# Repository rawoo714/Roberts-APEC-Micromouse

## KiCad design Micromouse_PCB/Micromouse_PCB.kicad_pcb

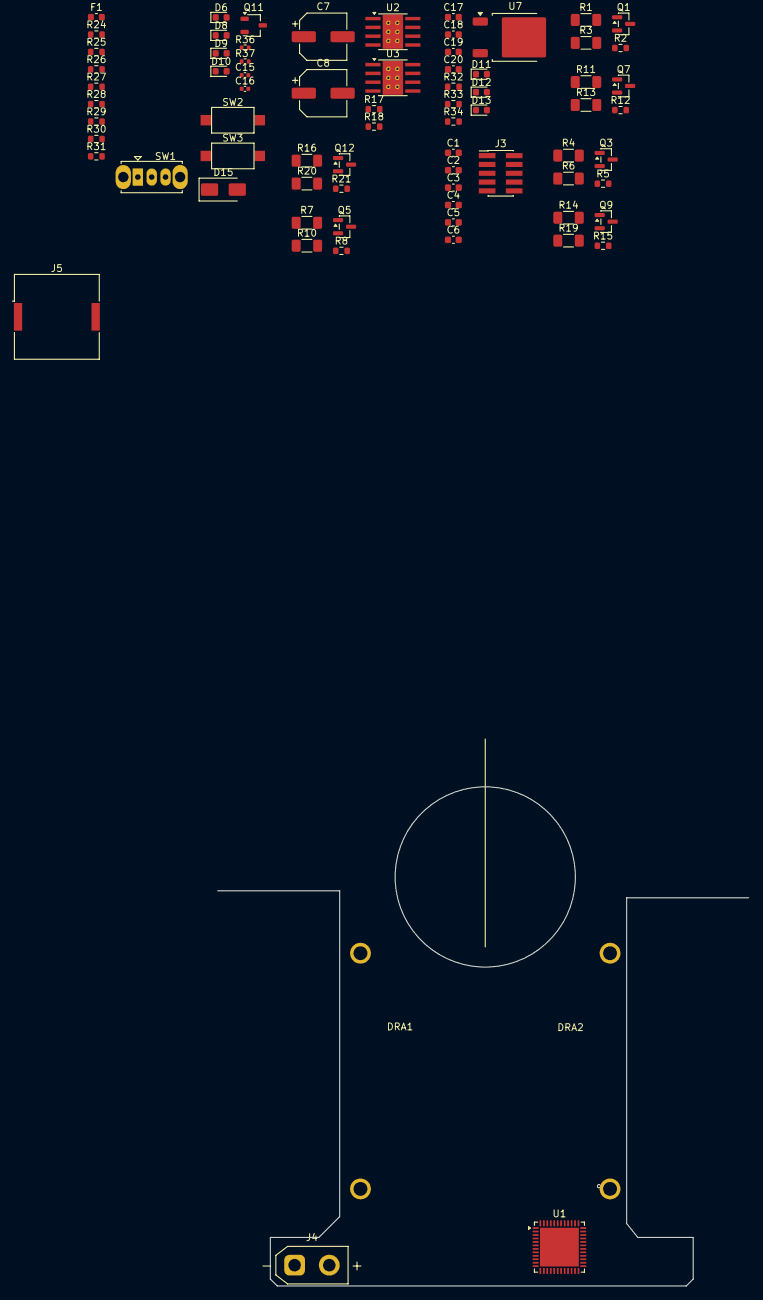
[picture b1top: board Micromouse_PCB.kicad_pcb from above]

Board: 4 copper layers, 76.6 x 72.0 mm, 75 parts (0 on the bottom side), 33 nets, no tracks yet.

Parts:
C1, C2, C3, C4, C5, C6: 100nF; C_0603_1608Metric
C7, C8: 220 uF; CP_Elec_6.3x5.9
C15: 1uF; C_0402_1005Metric
C16: 100nF; C_0402_1005Metric
C17, C19: 10uF; C_0603_1608Metric
C18, C20: 22uF; C_0603_1608Metric
D6: WHITE_LED; D_0603_1608Metric
D8: YELLOW_LED; D_0603_1608Metric
D9: Purple_LED; D_0603_1608Metric
D10: Red_LED; D_0603_1608Metric
D11, D12, D13: Blue_LED; LED_0603_1608Metric
D15: SMAJ15A; D_SMA
DRA1, DRA2: DIN_Rail_Adapter; Micromouse V.2 motor + wheels
F1: 5A 32V; Fuse_0603_1608Metric
J3: ARM Cortex Debug; PinHeader_2x05_P1.27mm_Vertical_SMD
J4: Power XT30UPB-M; AMASS_XT30UPB-F_1x02_P5.0mm_Vertical
J5: ALARM PKLCS1212E; Buzzer_Murata_PKLCS1212E
Q1, Q3, Q5, Q7, Q9, Q12: DMG3402LQ; SOT-23
Q11: DMG3402LQ; TSOT-23
R1, R4, R7, R11, R14, R20: 10k; R_1206_3216Metric_Pad1.30x1.75mm_HandSolder
R2, R5, R8, R12, R15, R21: 50Ω 1.5W; R_0603_1608Metric
R3, R6, R10, R13, R16, R19: 3.3k; R_1206_3216Metric_Pad1.30x1.75mm_HandSolder
R17, R18: 43 kΩ; R_0603_1608Metric
R24, R25, R26, R27, R28, R29, R33: 470Ω; R_0603_1608Metric
R30: 100kΩ; R_0603_1608Metric
R31: 40kΩ; R_0603_1608Metric
R32: 300Ω; R_0603_1608Metric
R34: 1kΩ; R_0603_1608Metric
R36: 10K; R_0402_1005Metric
R37: 100; R_0402_1005Metric
SW1: SW_SPDT; SW_Slide_SPDT_Straight_CK_OS102011MS2Q
SW2, SW3: SW_Push; SW_SPST_CK_RS282G05A3
U1: STM32WB55CCUx; QFN-48-1EP_7x7mm_P0.5mm_EP5.6x5.6mm
U2, U3: DRV8871DDA; Texas_HTSOP-8-1EP_3.9x4.9mm_P1.27mm_EP2.95x4.9mm_Mask2.4x3.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
U7: NCP1117-1.5_TO252; TO-252-2

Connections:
+3V3: C1.1, C2.1, C3.1, C4.1, C5.1, C6.1, C15.1, C16.1, C18.1, J3.1 (VCC), J5.1, R28.1, R29.1, R32.2
+5V: C17.2, C20.1, R33.2, U7.2 (VO)
/STM32F105RCT6/PA3: Q12.1 (G), R20.1
/STM32F105RCT6/PA4: Q1.1 (G), R1.1
/STM32F105RCT6/PA5: Q3.1 (G), R4.1
/STM32F105RCT6/PA6: Q5.1 (G), R7.1
/STM32F105RCT6/PA7: Q7.1 (G), R11.1
/STM32F105RCT6/PA10: R36.2, R37.1
/STM32F105RCT6/PC0: R30.1, R31.2
/STM32F105RCT6/PC4: Q9.1 (G), R14.1
/STM32F105RCT6/PC14: R29.2, SW3.1
/STM32F105RCT6/PC15: R28.2, SW2.1
GND: C1.2, C2.2, C3.2, C4.2, C5.2, C6.2, C7.2, C8.2, C15.2, C16.2, C17.1, C18.2, C19.1, C20.2, D6.1 (K), D8.1 (K), D9.1 (K), D10.1 (K), D11.1 (K), D12.1 (K), D13.1 (K), D15.2 (A2), J3.3 (GND), J3.5 (GND), J3.9 (GND_Detect), J4.1, Q1.2 (S), Q3.2 (S), Q5.2 (S), Q7.2 (S), Q9.2 (S), Q11.2 (S), Q12.2 (S), R1.2, R3.2, R4.2, R6.2, R7.2, R10.2, R11.2, R13.2, R14.2, R16.2, R17.2, R18.2, R19.2, R20.2, R30.2, R36.1, SW1.3 (C), SW2.2, SW3.2, U2.1 (GND), U2.7 (GND), U2.9 (GND), U3.1 (GND), U3.7 (GND), U3.9 (GND), U7.1 (GND)
unnamed: D6.2 (A), R25.2
unnamed: D8.2 (A), R26.2
unnamed: D9.2 (A), R27.2
unnamed: D10.2 (A), R24.2
unnamed: D11.2 (A), R32.1
unnamed: D12.2 (A), R33.1
unnamed: D13.2 (A), R34.1
unnamed: J4.2, SW1.2 (B)
unnamed: J5.2, Q11.3 (D)
unnamed: Q1.3 (D), R2.2
unnamed: Q3.3 (D), R5.2
unnamed: Q5.3 (D), R8.2
unnamed: Q7.3 (D), R12.2
unnamed: Q9.3 (D), R15.2
unnamed: Q11.1 (G), R37.2
unnamed: Q12.3 (D), R21.2
unnamed: F1.1, SW1.1 (A)
unnamed: R18.1, U2.4 (ILIM)
unnamed: R17.1, U3.4 (ILIM)
VBUS: C7.1, C8.1, C19.2, D15.1 (A1), F1.2, R31.1, R34.2, U2.5 (VM), U3.5 (VM), U7.3 (VI)
